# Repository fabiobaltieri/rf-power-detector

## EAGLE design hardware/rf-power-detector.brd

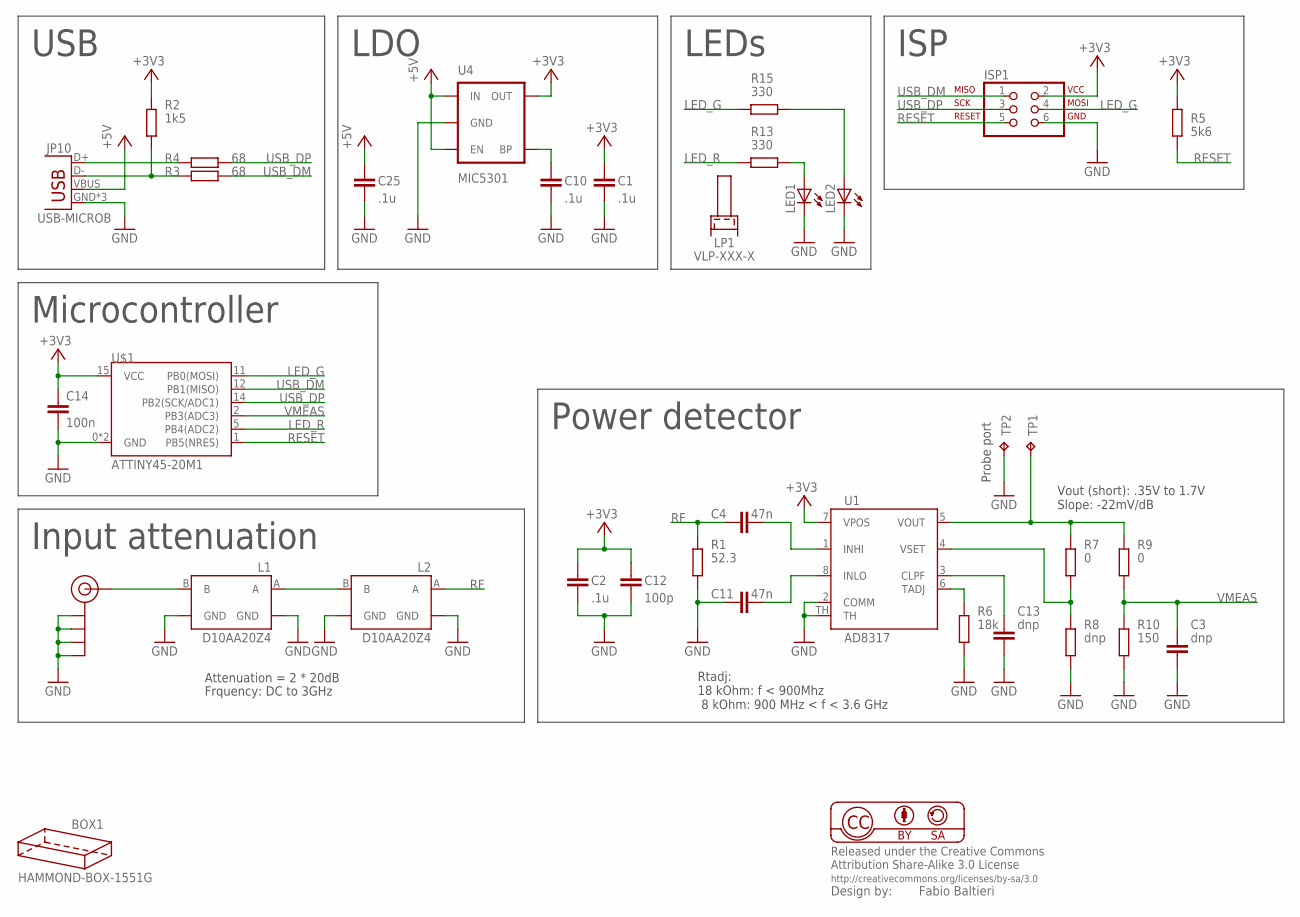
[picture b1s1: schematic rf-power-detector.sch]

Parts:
BOX1: HAMMOND-BOX-1551G; 1551G
C1, C2, C10, C25: .1u; C0603
C3, C13: dnp; C0603
C4, C11: 47n; C0603
C12: 100p; C0603
C14: 100n; C0603
ISP1: ISP-AVR910PTH; 2X03
J$1: SMA_EDGE; SMA-EDGE
JP10: USB-MICROB
L1, L2: D10AA20Z4; D10AAXXZ4
LED1, LED2: LEDSML0805; SML0805
LP1: VLP-XXX-X
R1: 52.3; R0603
R2: 1k5; R0603
R3, R4: 68; R0603
R5: 5k6; R0603
R6: 18k; R0603
R7, R9: 0; R0603
R8: dnp; R0603
R10: 150; R0603
R13, R15: 330; R0603
TP1, TP2: TPPAD1-13; P1-13
U1: AD8317; LFCSP8
U4: MIC5301; SOT23-5
U$1: ATTINY45-20M1; QFN20

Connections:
+3V3: C1.1, C2.1, C12.1, C14.1, ISP1.2, R2.2, R5.1, U1.7 (VPOS), U4.5 (OUT), U$1.15 (VCC)
+5V: C25.1, JP10.VBUS, U4.1 (IN), U4.3 (EN)
GND: C1.2, C2.2, C3.2, C10.2, C11.1, C12.2, C13.2, C14.2, C25.2, ISP1.6, J$1.GND@0 (GND), J$1.GND@1 (GND), J$1.GND@2 (GND), J$1.GND@3 (GND), JP10.GND, JP10.MT1 (GND), JP10.MT2 (GND), L1.GND@0 (GND), L1.GND@1 (GND), L2.GND@0 (GND), L2.GND@1 (GND), LED1.C, LED2.C, R1.1, R6.1, R8.1, R10.1, TP2.TP, U1.2 (COMM), U1.TH, U4.2 (GND), U$1.0 (GND), U$1.8 (GND)
LED_G: ISP1.4, R15.2, U$1.11 (PB0(MOSI))
LED_R: R13.2, U$1.5 (PB4(ADC2))
unnamed: JP10.D+, R4.2
unnamed: J$1.SIG (SIGNAL), L1.B
unnamed: LED1.A, R13.1
unnamed: L1.A, L2.B
unnamed: C4.2, U1.1 (INHI)
unnamed: C11.2, U1.8 (INLO)
unnamed: JP10.D-, R2.1, R3.2
unnamed: C10.1, U4.4 (BP)
unnamed: R6.2, U1.6 (TADJ)
unnamed: C13.1, U1.3 (CLPF)
unnamed: R7.1, R8.2, U1.4 (VSET)
unnamed: R7.2, R9.2, TP1.TP, U1.5 (VOUT)
unnamed: LED2.A, R15.1
RESET: ISP1.5, R5.2, U$1.1 (PB5(NRES))
RF: C4.1, L2.A, R1.2
USB_DM: ISP1.1, R3.1, U$1.12 (PB1(MISO))
USB_DP: ISP1.3, R4.1, U$1.14 (PB2(SCK/ADC1))
VMEAS: C3.1, R9.1, R10.2, U$1.2 (PB3(ADC3))

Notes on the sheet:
ISP
LEDs
LDO
USB
Microcontroller
Probe port
Input attenuation
Power detector
Attenuation = 2 * 20dB
Frquency: DC to 3GHz
Rtadj: 18 kOhm: f < 900Mhz 8 kOhm: 900 MHz < f < 3.6 GHz
Vout (short): .35V to 1.7V Slope: -22mV/dB

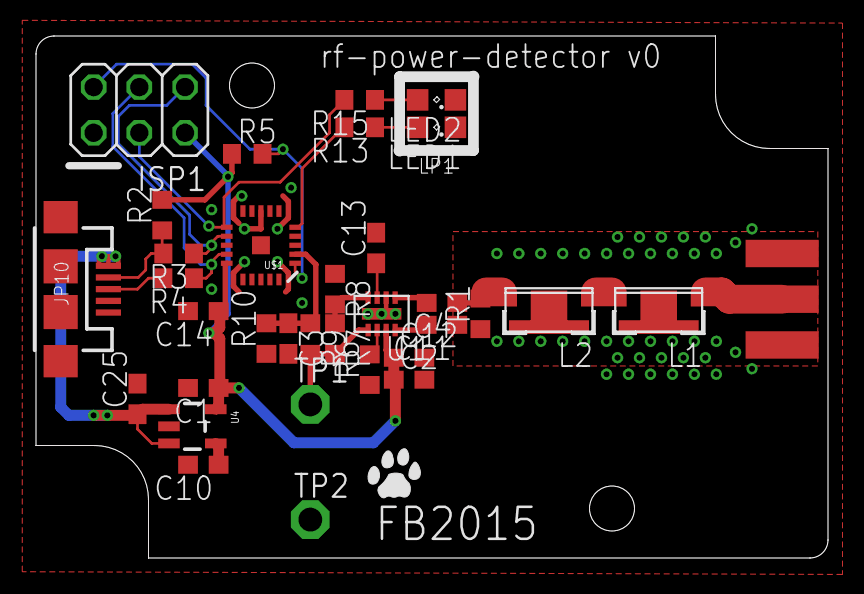
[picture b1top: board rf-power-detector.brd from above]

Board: 2 copper layers, 44.0 x 29.0 mm, 37 parts (0 on the bottom side), 23 nets.

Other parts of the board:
U$2: CAT-L

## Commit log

2015-10-08 hw: initial import, r0
2016-01-17 fw: initial import
2016-01-17 hw: add a 150Ohm load on the adc input
2016-01-18 fw: add a request for reporting the fixed pad value
2016-01-18 cmdline: initial import
2016-01-26 cmdline: fix help text
2016-01-26 cmdline: add no signal/overload indication
2016-02-03 change usb device name to rf-power-detector
2016-02-06 cmdline: move the host side code in librfpower.a

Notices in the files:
parts and their libraries:
SparkFun-Connectors: Licensing: CC v3.0 Share-Alike You are welcome to use this library for commercial purposes.
balto: Released under the Creative Commons
balto: http://creativecommons.org/licenses/by-sa/3.0
